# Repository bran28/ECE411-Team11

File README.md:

# ECE411-Team11
ECE 411 -Team 11 practicum project.

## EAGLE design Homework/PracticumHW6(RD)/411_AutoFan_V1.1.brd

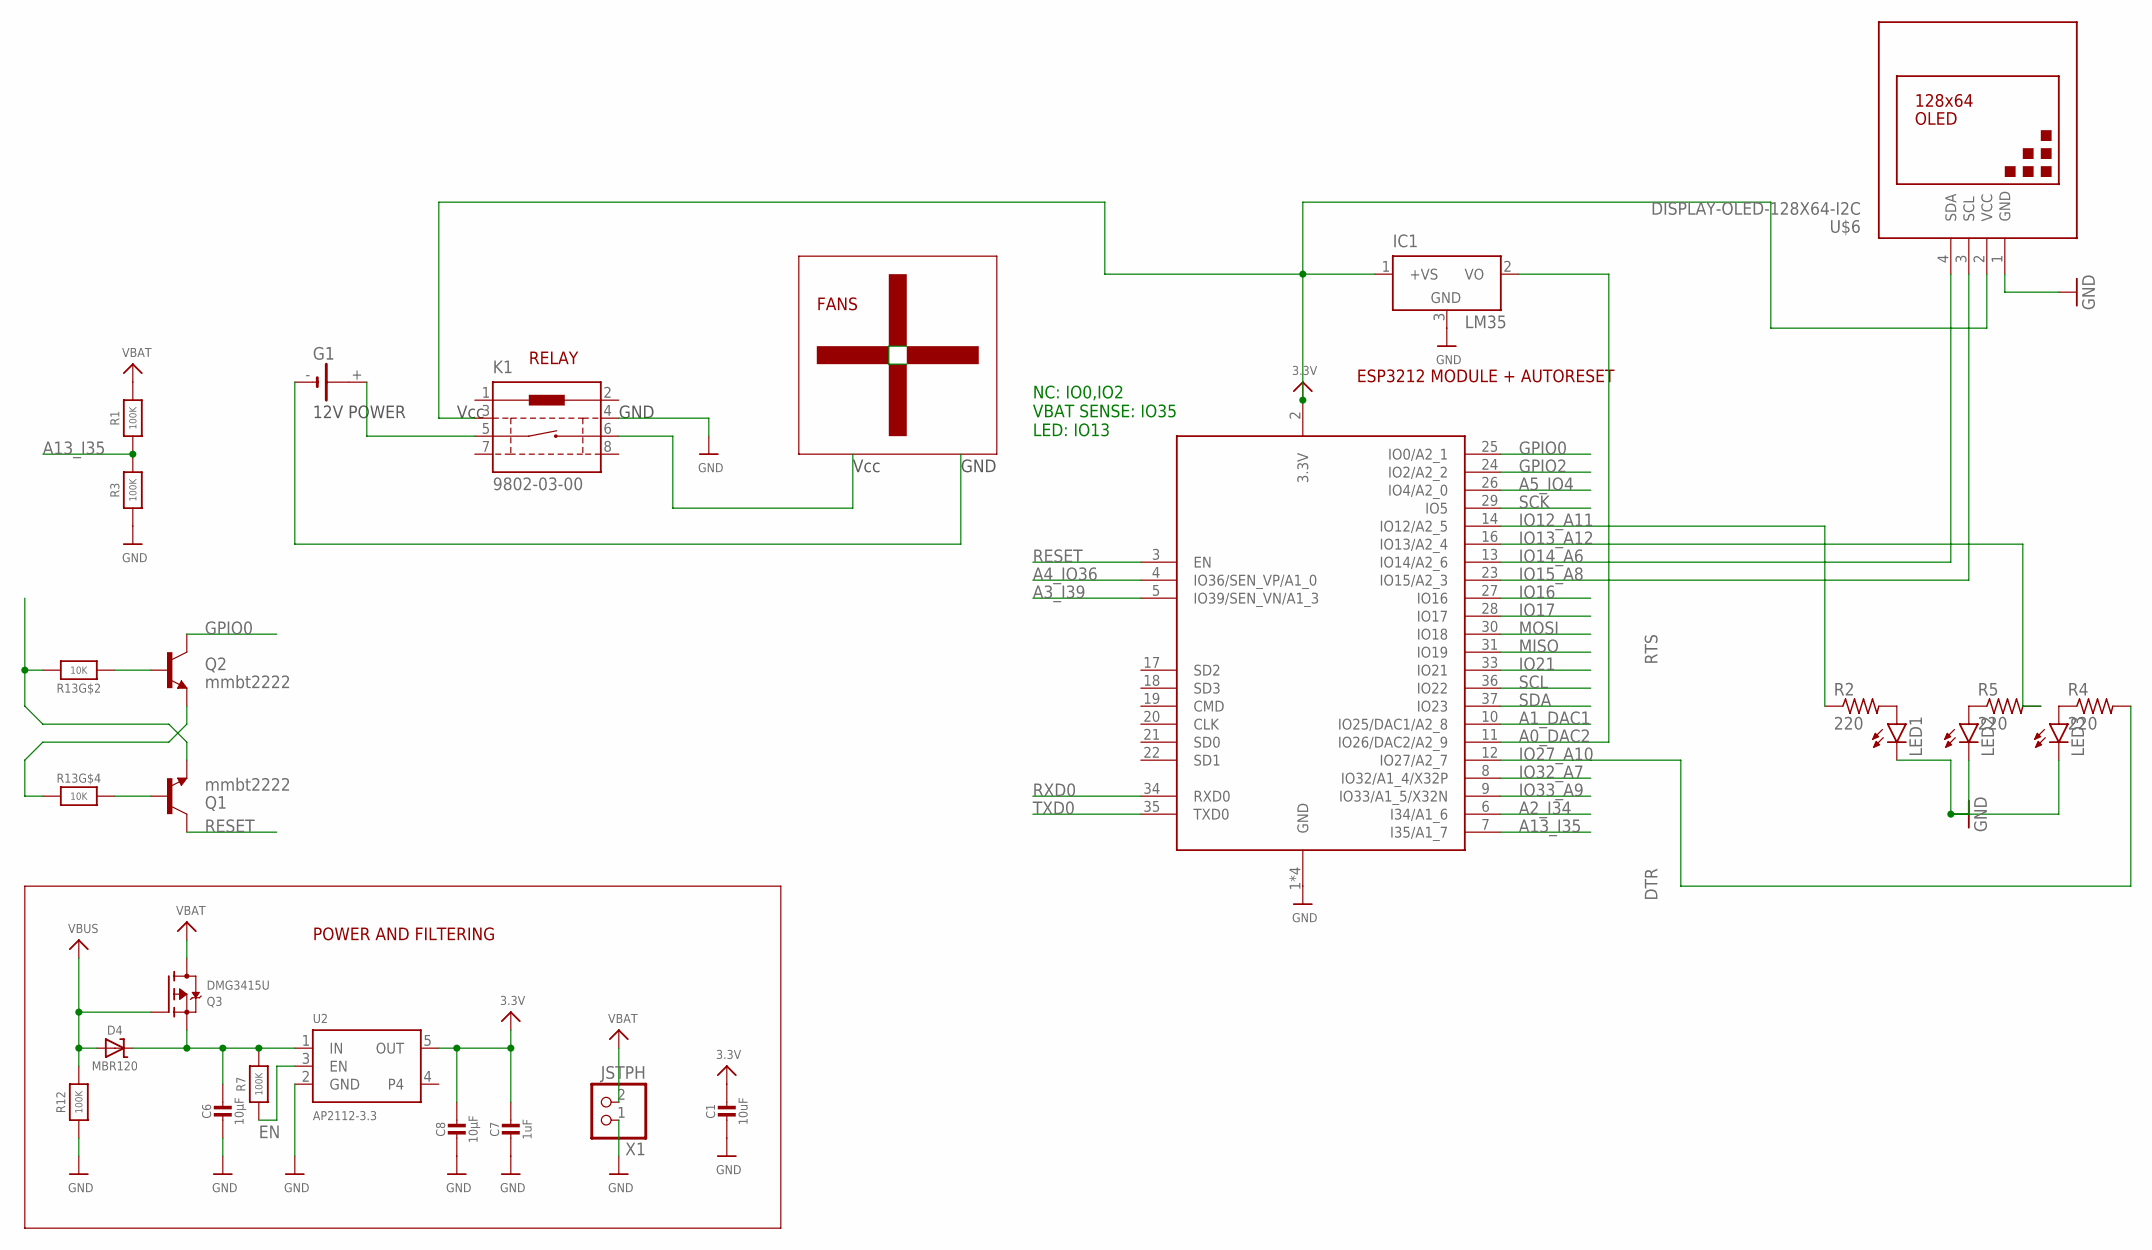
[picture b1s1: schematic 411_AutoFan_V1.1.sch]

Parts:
C1: 10uF; 0805-NO
C6, C8: 10µF; 0805-NO
C7: 1uF; 0603-NO
D4: MBR120; SOD-123
G1: CR2032V
IC1: LM50; SOT23
K1: 9802-03-00; 9802-00
LED1, LED2, LED3: LED5MM
Q1, Q2: mmbt2222; SOT23-3
Q3: DMG3415U; SOT23-R
R1, R3, R7, R12: 100K; 0603-NO
R2, R4, R5: 220; 0204/7
R13: 10K; RESPACK_4X0603
U2: AP2112-3.3; SOT23-5
U$6: DISPLAY-OLED-128X64-I2C
X1: JSTPH; JSTPH2
X2: ESP32_WROOM32_SKINNY; WROOM32_SKINNY

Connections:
A0_DAC2: IC1.2 (VO), X2.11 (IO26/DAC2/A2_9)
A1_DAC1: X2.10 (IO25/DAC1/A2_8)
A2_I34: X2.6 (I34/A1_6)
A3_I39: X2.5 (IO39/SEN_VN/A1_3)
A4_IO36: X2.4 (IO36/SEN_VP/A1_0)
A5_IO4: X2.26 (IO4/A2_0)
A13_I35: R1.1, R3.2, X2.7 (I35/A1_7)
DTR: Q2.2 (E), R13.4 (1)
EN: R7.1, U2.3 (EN)
GND: C1.2, C6.2, C7.2, C8.2, IC1.3 (GND), K1.4, LED1.K (C), LED2.K (C), LED3.K (C), R3.1, R12.1, U2.2 (GND), U$6.1 (GND), X1.1, X2.1 (GND), X2.15 (GND), X2.38 (GND), X2.P$1 (GND)
GPIO2: X2.24 (IO2/A2_2)
IO12_A11: R2.1, X2.14 (IO12/A2_5)
IO13_A12: R5.2, X2.16 (IO13/A2_4)
IO14_A6: U$6.4 (SDA), X2.13 (IO14/A2_6)
IO15_A8: U$6.3 (SCL), X2.23 (IO15/A2_3)
IO16: X2.27 (IO16)
IO17: X2.28 (IO17)
IO21: X2.33 (IO21)
IO27_A10: R4.2, X2.12 (IO27/A2_7)
IO32_A7: X2.8 (IO32/A1_4/X32P)
IO33_A9: X2.9 (IO33/A1_5/X32N)
MISO: X2.31 (IO19)
MOSI: X2.30 (IO18)
unnamed: LED1.A, R2.2
unnamed: LED3.A, R4.1
unnamed: LED2.A, R5.1
unnamed: C6.1, D4.C, Q3.2 (S), R7.2, U2.1 (IN)
unnamed: G1.+, K1.5
unnamed: Q1.1 (B), R13.5 (2)
unnamed: Q2.1 (B), R13.2 (1)
RESET: Q1.3 (C), X2.3 (EN)
RTS: Q1.2 (E), R13.7 (2)
RXD0: X2.34 (RXD0)
SCK: X2.29 (IO5)
SCL: X2.36 (IO22)
SDA: X2.37 (IO23)
TXD0: X2.35 (TXD0)
VBAT: Q3.3 (D), R1.2, X1.2
VBUS: D4.A, Q3.1 (G), R12.2

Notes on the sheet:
ESP3212 MODULE + AUTORESET
NC: IO0,IO2 VBAT SENSE: IO35 LED: IO13
POWER AND FILTERING
LM35
Vcc
GND
12V POWER
FANS
RELAY

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
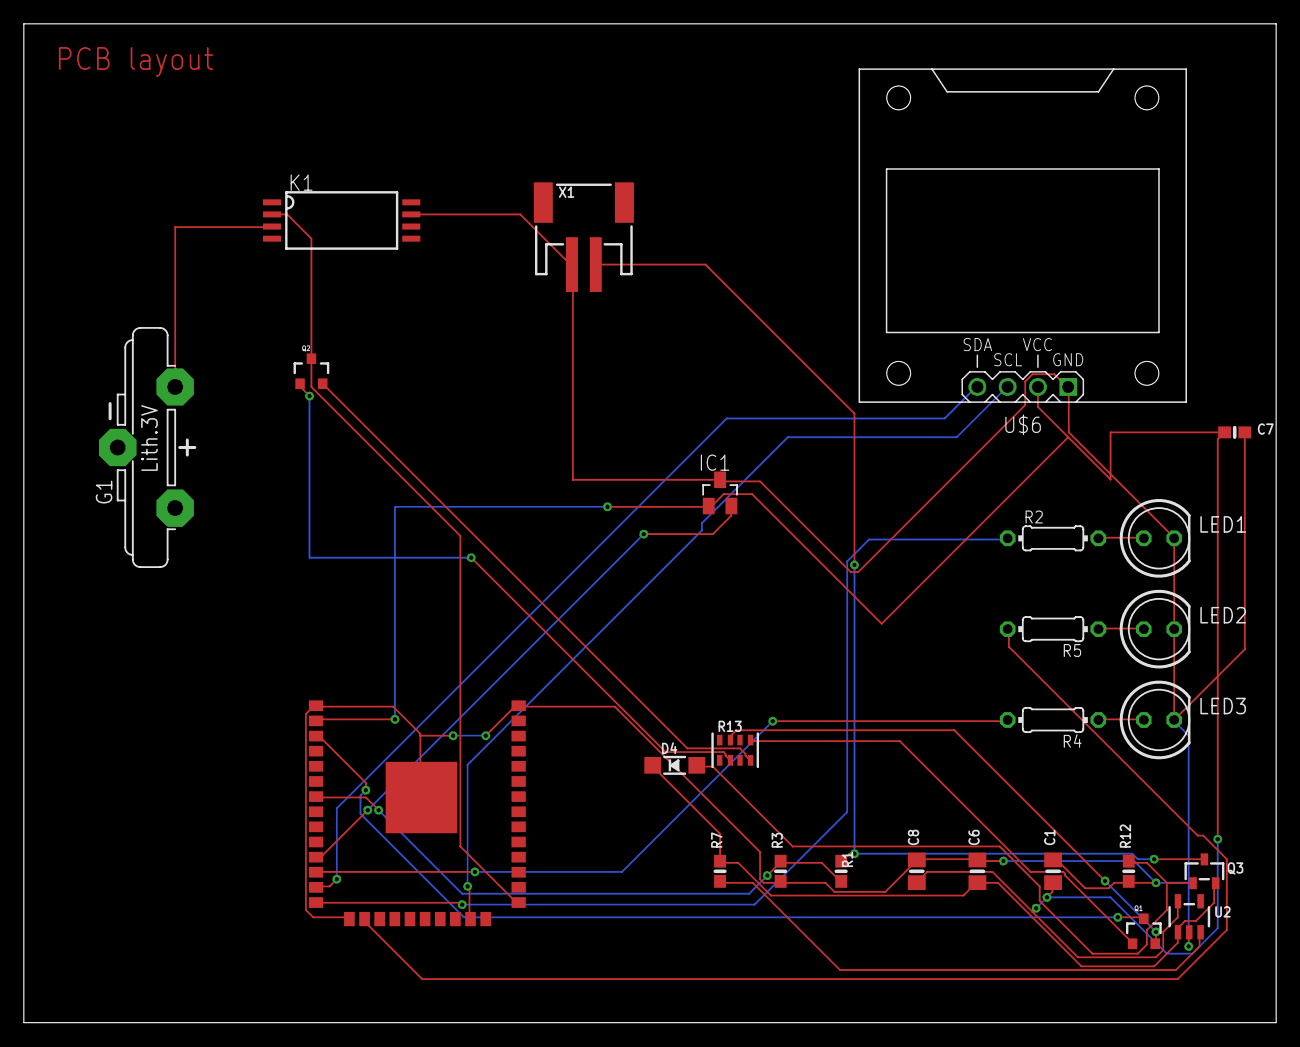
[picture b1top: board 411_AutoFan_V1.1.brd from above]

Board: 2 copper layers, 105.1 x 83.8 mm, 26 parts (0 on the bottom side), 23 nets.

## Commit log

2020-11-02 Create PCB Design
2020-11-02 Create Breadboard Prototype
2020-11-02 Create PrototypeVideo Link
2020-11-05 Rename Descreiption
2020-11-05 Rename
2020-11-11 Sch update
2020-11-19 Add files via upload
    Final Schematic Version 1.3
2020-11-19 Upload 3D and peer review
2020-11-19 Create Final Schematic
2020-12-03 Create Homework
2020-12-03 Create empty
2020-12-03 moved PDS in HW
2020-12-03 Moving files to HW folder
2020-12-03 Organzing HW files
2020-12-03 Version updated
2020-12-04 Practicum HW's updated
2020-12-04 Homework Files re-organized
2020-12-04 Renamed File
2020-12-04 Create HW 6 SCH+BRD RD

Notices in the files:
parts and their libraries:
microbuilder: This work is placed in the public domain, and may be freely used for commercial and non-commercial work with the following conditions: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
SparkFun: Licensing: CC v3.0 Share-Alike You are welcome to use this library for commercial purposes.
